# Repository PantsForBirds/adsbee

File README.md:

# ADSBee

ADSBee is a family of open-source, dual-band ADS-B receivers from [Pants for Birds LLC](https://pantsforbirds.com). Every ADSBee decodes 1090 MHz Mode S / ADS-B and 978 MHz UAT transmissions onboard — no SDR dongle, FPGA, or host computer required — maintains an aircraft dictionary, and streams tracked aircraft over UART (and, on the 1090 family, WiFi / Ethernet) in a wide range of output protocols. This repository holds the firmware, hardware design files, datasheets, and host software for the whole family.

There are two product lines, which share most of their firmware (`firmware/common/`):

| | **ADSBee 1090** | **ADSBee 1421** |
|---|---|---|
| Best for | Ground stations, feeders, networked receivers | Ultra-low-power embedded / UAS detect-and-avoid |
| Processors | RP2040 + ESP32-S3 + CC1312 | TI CC1314R10 + Semtech LR2021 |
| 1090 MHz | Custom RF frontend + RP2040 PIO decoder | LR2021 OOK receiver |
| 978 MHz UAT | CC1312 sub-GHz radio | CC1314 sub-GHz radio (uplink reception selectable) |
| Interfaces | USB, UART, WiFi, Ethernet (PoE pant / W5500), GNSS | UART (AT commands), SYNC line, LR2021 SPI passthrough |
| Power | ~1W | ~19 mA at 1.8–3.3 V |
| Firmware | [`firmware/adsbee_1090/`](firmware/adsbee_1090/) | [`firmware/adsbee_1421/`](firmware/adsbee_1421/) |

## Safety Notice

We work hard to make ADSBee products performant and reliable, but not all aircraft broadcast their location, messages can be lost or corrupted, and hardware or software can fail. ADSBee cannot guarantee detection or accurate reporting of all traffic. Users are responsible for evaluating its suitability for their application and for the safe operation of any system it is integrated into. See our [terms of sale](https://pantsforbirds.com/terms-of-sale/#warranty) and [license](LICENSE) for full terms.

## Products and Where to Buy

All ADSBee devices are designed and sold by Pants for Birds LLC. Purchasing a device is the best way to support the project. Product pages, datasheets, and the [Quick Start Guide](https://pantsforbirds.com/adsbee/quick-start/) live at [pantsforbirds.com](https://pantsforbirds.com/adsbee/).

### ADSBee 1090 family

| | |
|---|---|
|  | **[ADSBee 1090U](https://pantsforbirds.com/product/adsbee-1090u/)** — RP2040, ESP32-S3, CC1312, and a custom 1090 MHz RF frontend on a single PCBA, enabling all multi-band receive and networking functions (Ethernet requires an external pant). [Datasheet](word/exports/datasheet_adsbee_1090.pdf) |
|  | **[ADSBee m1090](https://pantsforbirds.com/product/adsbee-m1090/)** — solder-down module containing only the 1090 MHz frontend and RP2040. Add a CC1312 and ESP32 on your carrier board for the full 1090U feature set, running the same firmware image. Drops one of the 1090U's two LNA stages for lower power and better ultra-close-range performance; populate an external LNA on the carrier for equivalent maximum range. An [m1090 Eval Board](https://pantsforbirds.com/product/adsbee-m1090-eval-board/) is available ([datasheet](word/exports/datasheet_adsbee_m1090_eval_board.pdf)). |
|  | **[GS3M PoE](https://pantsforbirds.com/product/adsbee-gs3m-poe/)** — the ADSBee 1090U in a ruggedized, weatherproof enclosure, connected and powered over 802.3af Power over Ethernet for industrial and outdoor installations. [Datasheet](word/exports/datasheet_gs3m_poe.pdf) |

### ADSBee 1421 family

| | |
|---|---|
|  | **[ADSBee m1421](https://pantsforbirds.com/product/adsbee-m1421/)** — high-performance, ultra-low-power dual-band receiver module (TI CC1314R10 + Semtech LR2021). Receives 1090 MHz Mode S and 978 MHz UAT, tracks up to 400 aircraft onboard, and reports over UART. Weighs 1.85 g. [Datasheet](word/exports/datasheet_adsbee_m1421.pdf) |
|  | **[ADSBee 1421 Developer Kit](https://pantsforbirds.com/product/adsbee-1421-devkit/)** — compact carrier board for the m1421 with a power combiner so a single lightweight dual-band antenna feeds both the 1090 MHz and 978 MHz inputs. Includes the PCBA with ARM-JTAG header, wire harness, USB programmer, and a dual-band ADS-B antenna. [Datasheet](word/exports/datasheet_adsbee_1421_devkit.pdf) |

## ADSBee 1090

ADSBee 1090 is an open-source multi-band radio receiver and decoder for ADS-B packets transmitted by aircraft and ground stations. It is based on an RP2040 microcontroller and utilizes two independent PIO blocks to find and decode ADS-B messages without the need for an FPGA. ADSBee 1090 includes a radio receiver frontend with filtering and amplification, as well as a software-defined comparator circuit with an adjustable trigger threshold for customizable receive sensitivity in a diverse range of RF environments.

### Features
* Decoding of 1090 MHz transponder signals (ADS-B and Mode S).
* Decoding of 978 MHz UAT transponder signals (ADS-B) and uplink data (FIS-B/TIS-B).
* ADS-L (EASA ADS-L 4 SRD-860) receive on 868.2 or 868.4 MHz instead of UAT (`AT+SUBG_MODE=ADSL_RX`). ADS-L traffic shows in Aircraft JSON, the web UI, GDL90 and RAW (`#ADL*`). Senders alternate between the two channels, so one channel hears about half of their messages. The sub-GHz input is matched for 978 MHz; use an 868 MHz antenna. Firmware 0.11.0-rc1 and later.
* 1x USB console input / output for changing parameters and transmitting data.
* 1x UART for reporting data or ingesting GNSS information.
* Built-in EEPROM for storing nonvolatile settings.
* Feature-rich AT command set for customizing baud rates, output data protocols, signal conditioning values, etc.
* Multiple supported output protocols:
    * Raw packets
    * MAVLINK1
    * MAVLINK2
    * GDL90
    * Mode S Beast
    * Aircraft JSON
    * CSBee (custom information-rich ASCII protocol)
* 2.4 GHz 802.11 radio for automatic streaming of decoded values to custom endpoints on the internet. No external compute required, just add WiFi and power!
* Ethernet interface (requires external PoE pant or W5500 IC).
* GNSS module connector for MLAT and ground station location information.
* ~1W power draw.

### Architecture
ADSBee 1090 utilizes some basic RF hardware (SAW filters, LNA, logarithmic power detector) to amplify the received pulse-position-modulated ADS-B waveform into a pulse train that is conditioned by a comparator and fed to a PIO input pin on the RP2040. The RP2040 utilizes two PIO state machines, one for preamble detection and one for Manchester decoding of the message body, to decode the ADS-B message. This offers significant cost and power savings over FPGA-based solutions that solve the same problem.

A filtered PWM output from the RP2040 can be used to adjust the bias of the data slicer comparator circuit on the output of the receive signal chain, allowing logarithmic adjustments in receiver sensitivity which can be used to filter out weaker ADS-B signals in congested environments or maximize sensitivity for increased receive range.

There are two devices connected to the RP2040 via a common SPI bus: a CC1312 for secondary band receive and an ESP32-S3 for networking functions.

The CC1312 can be tuned to a variety of sub-GHz frequencies to decode UAT messages (and potentially more protocols in the future). These messages are forwarded to the RP2040 over SPI and reported through a unified interface along with the Mode S packets received by the RP2040.

The ESP32-S3 ingests raw packets from the RP2040 and maintains its own aircraft dictionary for reporting over network interfaces (WiFi, Ethernet). The RP2040's dictionary holds 400 aircraft for its USB and UART outputs; the ESP32-S3's holds 200.

All three microcontrollers utilize code stored on the RP2040's external flash chip, so firmware updates are conducted by flashing a single firmware image to the RP2040, which in turn flashes updated firmware images to the CC1312 and ESP32-S3.

## ADSBee 1421

ADSBee 1421 is an ultra-low-power dual band ADS-B receiver, built around a TI CC1314R10 low-power RF MCU and a Semtech LR2021 radio. The LR2021 provides best-in-class sensitivity for the high-baud-rate OOK 1090 MHz Mode S waveform, while the CC1314's sub-GHz RF core receives 978 MHz UAT and its Cortex-M33 does all demodulation, FEC, decoding, and aircraft tracking. The whole receiver draws about 19 mA and weighs under 2 g, making it suited to UAS detect-and-avoid and other power- and weight-constrained applications.

### Features
* Decoding of 1090 MHz transponder signals (ADS-B and Mode S), with selectable preamble modes for range vs. message-type coverage (`AT+R1090_PREAMBLE`).
* Decoding of 978 MHz UAT transponder signals (ADS-B) and ground uplink data (FIS-B/TIS-B). Uplink reception can be disabled independently (`AT+SUBG_MODE=UAT_RX_NO_UPLINK`) to save airtime and CPU when only traffic is needed.
* ADS-L (EASA ADS-L 4 SRD-860) receive on 868.2 or 868.4 MHz instead of UAT (`AT+SUBG_MODE=ADSL_RX`), reported in Aircraft JSON, GDL90 and RAW (`#ADL*`). The m1421 sub-GHz filter passes 770-928 MHz. Firmware 0.5.0-rc1 and later.
* Onboard aircraft dictionary for up to 400 simultaneous targets.
* UART console with a feature-rich AT command set (baud rate, output protocol, receiver position, gain, logging, …); settings persist in flash.
* Multiple supported output protocols: Raw packets, CSBee, MAVLINK1, MAVLINK2, GDL90, Mode S Beast, Aircraft JSON.
* SYNC line for host-controlled deep sleep (STANDBY with SRAM retained), which also hands the LR2021 SPI bus to an external MCU — e.g. to use the LR2021's 2.4 GHz radio for LoRa or mesh networking.
* Firmware updates over the UART ROM bootloader (no debugger needed) or JTAG. Holding SYNC high through a reset enters the bootloader, so any host that drives a USB-UART adapter's RTS → SYNC and DTR → RESET_N (or the included ADSBee 1421 Programmer) can reflash the module remotely. See [Reflashing over UART: the SYNC bootloader backdoor](firmware/adsbee_1421/README.md#reflashing-over-uart-the-sync-bootloader-backdoor).
* Ultra-low power: ~19 mA at 1.8–3.3 V.

### Architecture
The CC1314R10 runs a NoRTOS super-loop: it polls the LR2021 over SPI for 1090 MHz OOK frames, services its own RF core's UAT receptions (ADS-B and uplink are distinguished by sync word, so uplink can be switched off at the radio), runs the shared Mode S / UAT decoders and aircraft dictionary from `firmware/common/`, and reports over the console UART. A host can suspend the device by driving SYNC high; on wake the receiver re-initializes itself. SYNC is also the ROM bootloader backdoor pin, so a reset while SYNC is high enters the serial bootloader. See [`firmware/adsbee_1421/AGENTS.md`](firmware/adsbee_1421/AGENTS.md) for the build guide and the SYNC sleep / LR2021 bus-handoff contract, and the [m1421 datasheet](word/exports/datasheet_adsbee_m1421.pdf) for the full AT command reference.

## Repository Layout

| Path | Contents |
|---|---|
| [`firmware/`](firmware/) | All firmware. [`adsbee_1090/`](firmware/adsbee_1090/) (RP2040 `pico/`, `esp/`, CC1312 `ti/`), [`adsbee_1421/`](firmware/adsbee_1421/) (CC1314 `ti/`, RP2040-Zero `programmer/`, the ADSBee 1421 Programmer), [`common/`](firmware/common/) (shared decoders, aircraft dictionary, comms, settings), `modules/` (submodules: cppAT, googletest, …), [`scripts/`](firmware/scripts/) (dev tooling), [`build.sh`](firmware/build.sh) dispatcher. |
| [`software/`](software/) | Host software: [`adsbee_1421_console/`](software/adsbee_1421_console/) (single-file Web Serial console + UART flasher for the 1421), `adsbee/` (Python package), `serial_logger/`, and `tar1090/` / `ultrafeeder/` / `ultra2/` feeder compose files. |
| [`ci/`](ci/) | Hardware-in-the-loop USB/UF2 + OTA flash test run by the self-hosted CI runner. |
| [`kicad/`](kicad/) | Hardware design files (ADSBee 1090, 1090U, frontend prototypes, panels). |
| [`3d/`](3d/) | Enclosure exports and CAD links. |
| [`ltspice/`](ltspice/), [`excel/`](excel/) | RF / analog simulations and design calculations. |
| [`affinity/`](affinity/) | Diagrams and promotional artwork sources. |
| [`word/`](word/) | Product datasheets and firmware reference guide (`.docx` sources, PDFs in [`word/exports/`](word/exports/)). |
| [`references/`](references/) | Protocol specifications and component datasheets. |
| [`images/`](images/) | Images used by this README. |

## Building and Flashing Firmware

All toolchains live in Docker containers, so the only host requirements are Docker and git.

```bash
git clone https://github.com/CoolNamesAllTaken/adsbee.git
cd adsbee
bash firmware/scripts/setup_dev.sh        # init submodules + install the pre-commit version-check hook
bash firmware/build.sh adsbee_1090        # RP2040 + ESP32-S3 + CC1312 -> combined.uf2
bash firmware/build.sh adsbee_1421        # CC1314R10 -> adsbee_1421-<version>.hex
```

* **[`firmware/README.md`](firmware/README.md)** — prerequisites, the build dispatcher, build targets and outputs.
* **[`firmware/AGENTS.md`](firmware/AGENTS.md)** — firmware architecture overview and the version-management rules.
* **ADSBee 1090:** [`firmware/adsbee_1090/Developers_Guide.md`](firmware/adsbee_1090/Developers_Guide.md) covers the three-processor build order, flashing (`combined.uf2` over USB BOOTSEL, or OTA through the ESP32 web interface), and recovery.
* **ADSBee 1421:** [`firmware/adsbee_1421/AGENTS.md`](firmware/adsbee_1421/AGENTS.md) covers the build; flash over JTAG with a J-Link ([`firmware/adsbee_1421/ti/README.md`](firmware/adsbee_1421/ti/README.md)), or over UART using the ROM bootloader ([SYNC bootloader backdoor](firmware/adsbee_1421/README.md#reflashing-over-uart-the-sync-bootloader-backdoor)) via the [ADSBee 1421 Programmer](firmware/adsbee_1421/programmer/README.md) (an RP2040-Zero board included in the Developer Kit), a host script driving RTS/DTR, or the **Upload Firmware** button in the [web console](software/adsbee_1421_console/README.md).

Prebuilt firmware is published on the [Releases page](https://github.com/CoolNamesAllTaken/adsbee/releases). Releases are tagged per product as `adsbee_1090-<major>.<minor>.<patch>` and `adsbee_1421-<major>.<minor>.<patch>` (release candidates carry an `-rcN` suffix). `AT+DEVICE_INFO?` reports the firmware version running on a device.

## Support, Bugs, and Feature Requests

* **Getting started / using a device:** start with the [Quick Start Guide](https://pantsforbirds.com/adsbee/quick-start/) and the product datasheets in [`word/exports/`](word/exports/) (AT command reference, reporting protocols, pinouts).
* **Purchasing, orders, warranty, and hardware support:** contact Pants for Birds through [pantsforbirds.com/contact](https://pantsforbirds.com/contact/).
* **Firmware / software bugs:** open a [GitHub Issue](https://github.com/CoolNamesAllTaken/adsbee/issues). Please include:
  * which product (1090U, m1090, GS3M PoE, m1421, 1421 Developer Kit) and the output of `AT+DEVICE_INFO?` (part code and firmware version);
  * what you expected vs. what happened, and steps to reproduce;
  * relevant console output (`AT+LOG_LEVEL=INFO` makes the device chattier) and, for the 1090 family, the web interface/feed configuration involved.
* **Feature requests and questions:** also welcome as GitHub Issues; please tag the title with the product family.

## Contributing

Contributions are welcome (bug fixes, new output protocols, decoder improvements, documentation, etc)! Please follow the steps below to contribute a change.

1. Fork the repo and create a branch from `main`.
2. Run `bash firmware/scripts/setup_dev.sh` once. It initializes submodules and installs a git pre-commit hook that enforces the version rule below.
3. Make your change. Any change under `firmware/adsbee_1090/`, `firmware/adsbee_1421/`, or `firmware/common/` must ship under a firmware version that has not been released yet for the affected product(s) (`firmware/common/coprocessor/object_dictionary.cpp` for 1090, `firmware/adsbee_1421/ti/object_dictionary/object_dictionary.cpp` for 1421; a `common/` change concerns both). If main is already on the next unreleased RC, keep it; if its version matches a release tag, move to the next unreleased RC. Note that devices only reflash coprocessors on a version mismatch, so you will need to force a reflash or bump the software version to test your code [`firmware/AGENTS.md`](firmware/AGENTS.md). When have finished testing and go to you submit your PR, ensure that your firmware version matches the version string in main! Firmware versions are only rolled upon each release.
4. If you add or change an AT command, reporting protocol, or other user-visible behavior, update the corresponding datasheet in [`word/`](word/).
5. Build locally with `firmware/build.sh` and, for 1090 changes, run the host unit tests (`bash firmware/build.sh adsbee_1090 test`).
6. Open a pull request against `main`. [CI](https://github.com/CoolNamesAllTaken/adsbee/actions/workflows/firmware.yml) builds every target and runs the unit tests; the hardware-in-the-loop flash test runs on `main` after merge.

By contributing you agree that your contributions are licensed under the GPL-3.0.

## License

ADSBee firmware, software, and design files in this repository are released under the [GNU General Public License v3.0](LICENSE). ADSBee is a product of Pants for Birds LLC.

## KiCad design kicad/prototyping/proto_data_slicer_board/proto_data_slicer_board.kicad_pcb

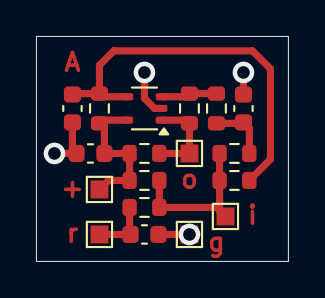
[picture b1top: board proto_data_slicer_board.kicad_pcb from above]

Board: 2 copper layers, 14.0 x 12.5 mm, 18 parts (0 on the bottom side), 8 nets.

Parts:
C1: 100pF; C_0603_1608Metric
C2: 0.1uF; C_0603_1608Metric
C3: 3pF; C_0603_1608Metric
C4: 10nF; C_0603_1608Metric
R1, R3, R4: 10k; R_0603_1608Metric
R2, R5: 1M; R_0603_1608Metric
R6, R7, R8: 1k; R_0603_1608Metric
TP1, TP2, TP3, TP4, TP5: TestPoint; TestPoint_Pad_1.0x1.0mm
U1: MCP6566; SOT-353_SC-70-5

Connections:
+3V3: C2.1, R2.1, R7.1, R8.1, TP5.1, U1.5 (V+)
/IN: R1.1, R3.1, R6.1, R7.2, TP1.1
/LEVEL: C1.1, R1.2, R2.2, U1.4 (-)
/OUT: R5.2, R8.2, TP2.1, U1.1
/PULSE: C3.1, R3.2, R4.1
/PULSE': R4.2, R5.1, U1.3 (+)
/RSSI: C4.1, R6.2, TP3.1
GND: C1.2, C2.2, C3.2, C4.2, TP4.1, U1.2 (V-)

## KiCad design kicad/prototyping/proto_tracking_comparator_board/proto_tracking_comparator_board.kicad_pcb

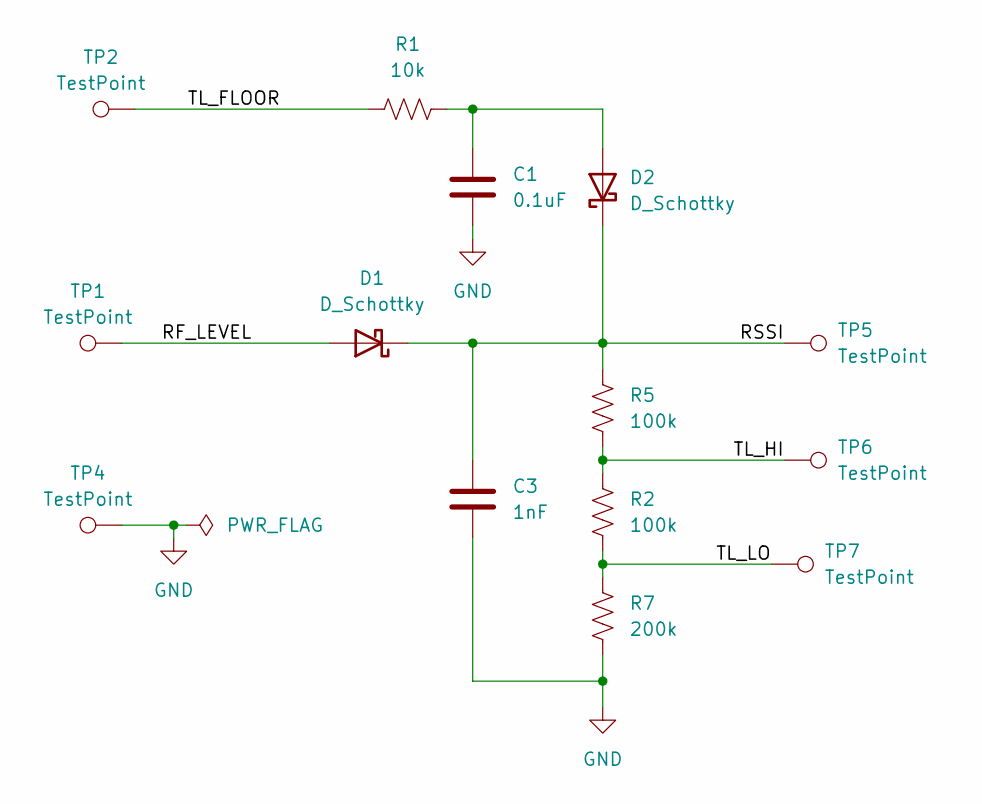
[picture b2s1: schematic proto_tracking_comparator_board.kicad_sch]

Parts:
C1: 0.1uF; C_0603_1608Metric
C3: 1nF; C_0603_1608Metric
D1, D2: D_Schottky; D_0402_1005Metric
R1: 10k; R_0603_1608Metric
R2, R5: 100k; R_0603_1608Metric
R7: 200k; R_0603_1608Metric
TP1, TP2, TP4, TP5, TP6, TP7: TestPoint; TestPoint_Pad_1.0x1.0mm

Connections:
/RF_LEVEL: D1.2 (A), TP1.1
/RSSI: C3.1, D1.1 (K), D2.1 (K), R5.2, TP5.1
/TL_FLOOR: R1.2, TP2.1
/TL_HI: R2.2, R5.1, TP6.1
/TL_LO: R2.1, R7.2, TP7.1
GND: C1.2, C3.2, R7.1, TP4.1
unnamed: C1.1, D2.2 (A), R1.1

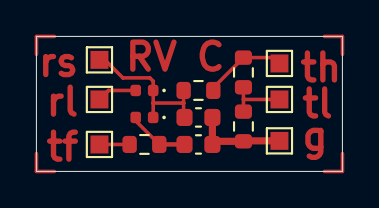
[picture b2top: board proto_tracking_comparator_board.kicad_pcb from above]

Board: 2 copper layers, 17.0 x 7.5 mm, 14 parts (0 on the bottom side), 7 nets.

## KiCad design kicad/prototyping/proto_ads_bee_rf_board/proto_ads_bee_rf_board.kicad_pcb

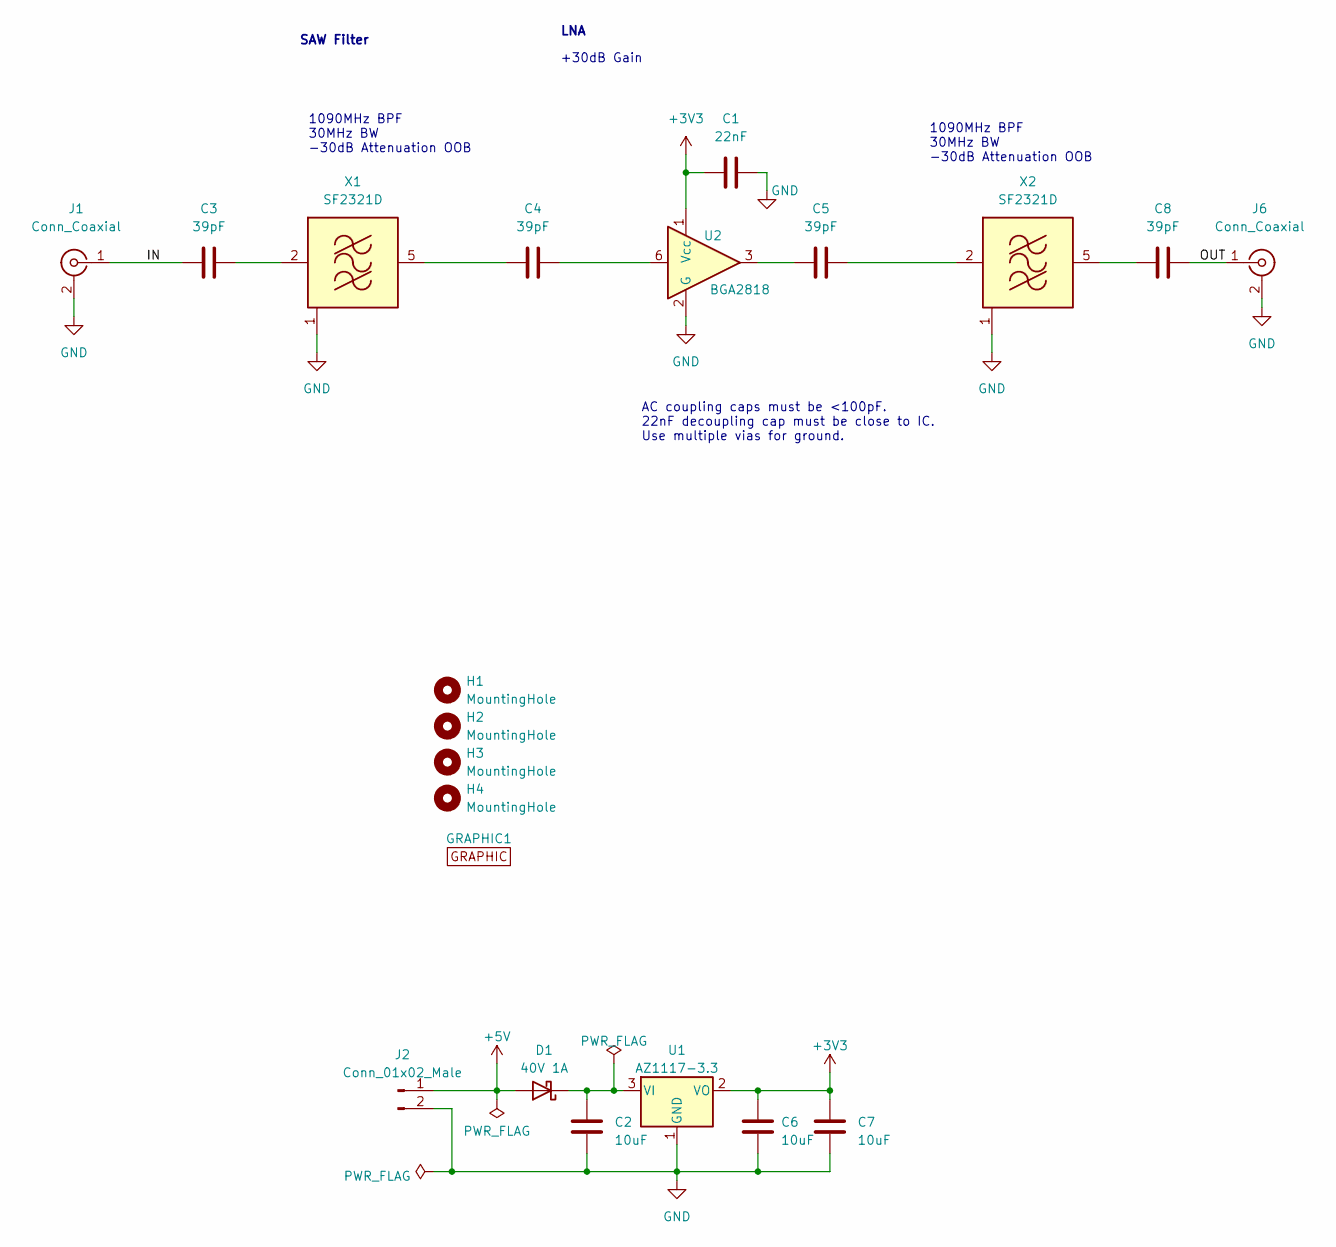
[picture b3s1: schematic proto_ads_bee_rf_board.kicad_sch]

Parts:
C1: 22nF; C_0603_1608Metric
C2, C6, C7: 10uF; C_0805_2012Metric
C3, C4, C5, C8: 39pF; C_0603_1608Metric
D1: 40V 1A; D_DO-41_SOD81_P7.62mm_Horizontal; MPN 1N5819
GRAPHIC1: Graphic; bird_with_pants_small_flipped
H1, H2, H3, H4: MountingHole; MountingHole_3.2mm_M3
J1, J6: Conn_Coaxial; SMA_Amphenol_132289_EdgeMount; MPN 132289
J2: Conn_01x02_Male; PinHeader_1x02_P2.54mm_Horizontal
U1: AZ1117-3.3; SOT-223-3_TabPin2
U2: BGA2818; SOT-363_SC-70-6
X1, X2: SF2321D; Filter_SAW-6_3.8x3.8mm; MPN SF2321D

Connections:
+3V3: C1.1, C6.1, C7.1, U1.2 (VO), U2.1 (Vcc)
+5V: D1.2 (A), J2.1
/IN: C3.1, J1.1 (In)
/OUT: C8.2, J6.1 (In)
GND: C1.2, C2.2, C6.2, C7.2, J1.2 (Ext), J2.2, J6.2 (Ext), U1.1 (GND), U2.2 (G), U2.4 (G), U2.5 (G), X1.1 (GND), X1.3 (GND), X1.4 (GND), X1.6 (GND), X2.1 (GND), X2.3 (GND), X2.4 (GND), X2.6 (GND)
unnamed: C4.2, U2.6
unnamed: C5.1, U2.3
unnamed: C2.1, D1.1 (K), U1.3 (VI)
unnamed: C3.2, X1.2 (IN)
unnamed: C4.1, X1.5 (OUT)
unnamed: C5.2, X2.2 (IN)
unnamed: C8.1, X2.5 (OUT)

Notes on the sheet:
LNA
+30dB Gain
1090MHz BPF 30MHz BW -30dB Attenuation OOB
SAW Filter
AC coupling caps must be <100pF. 22nF decoupling cap must be close to IC. Use multiple vias for ground.

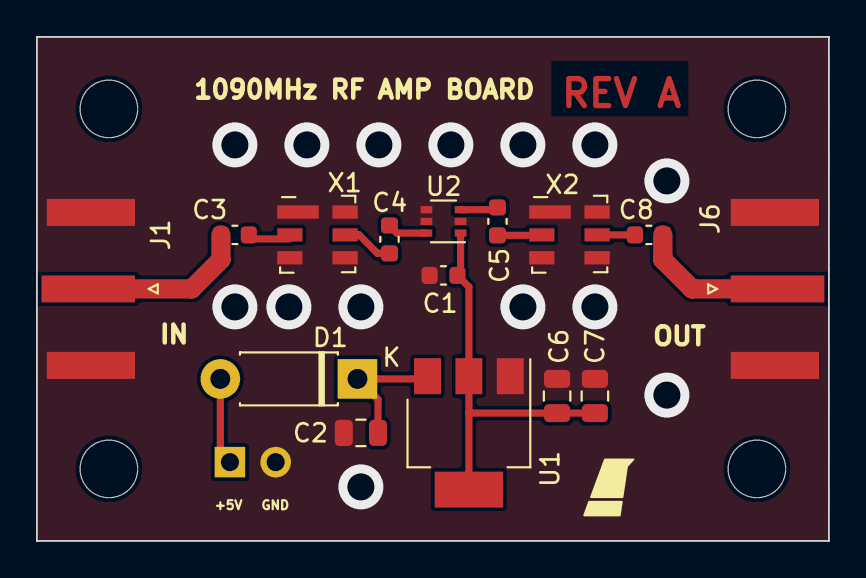
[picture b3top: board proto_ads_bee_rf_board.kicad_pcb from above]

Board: 2 copper layers, 44.0 x 28.0 mm, 21 parts (1 on the bottom side), 12 nets.

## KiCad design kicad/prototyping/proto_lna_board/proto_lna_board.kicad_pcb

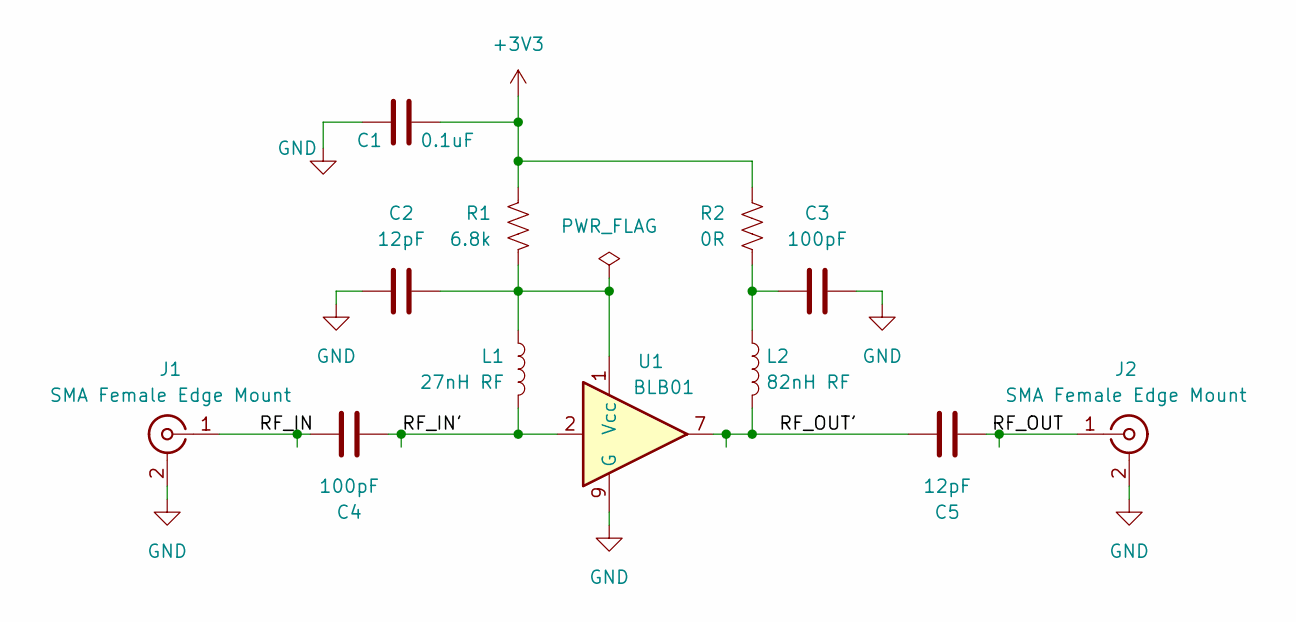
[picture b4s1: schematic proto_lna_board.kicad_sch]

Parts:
C1: 0.1uF; C_0402_1005Metric; MPN C60474
C2, C5: 12pF; C_0402_1005Metric; MPN C326662
C3, C4: 100pF; C_0402_1005Metric; MPN C106200
J1, J2: SMA Female Edge Mount; SMA_Amphenol_132289_EdgeMount
L1: 27nH RF; L_0402_1005Metric; MPN C408697
L2: 82nH RF; L_0402_1005Metric; MPN C54972
R1: 6.8k; R_0402_1005Metric; MPN C93940
R2: 0R; R_0402_1005Metric; MPN C60485
U1: BLB01; DFN-8-1EP_2x2mm_P0.5mm_EP0.9x1.5mm

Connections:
+3V3: C1.1, R1.1, R2.1
/RF_IN: C4.1, J1.1 (In)
/RF_IN': C4.2, L1.2, U1.2
/RF_OUT: C5.2, J2.1 (In)
/RF_OUT': C5.1, L2.2, U1.7
GND: C1.2, C2.1, C3.2, J1.2 (Ext), J2.2 (Ext), U1.9 (G)
unnamed: C3.1, L2.1, R2.2
unnamed: C2.2, L1.1, R1.2, U1.1 (Vcc)

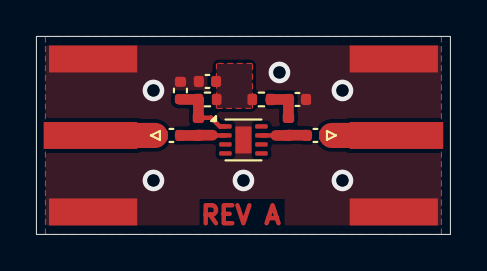
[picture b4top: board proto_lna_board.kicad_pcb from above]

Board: 2 copper layers, 23.0 x 11.0 mm, 12 parts (0 on the bottom side), 8 nets.

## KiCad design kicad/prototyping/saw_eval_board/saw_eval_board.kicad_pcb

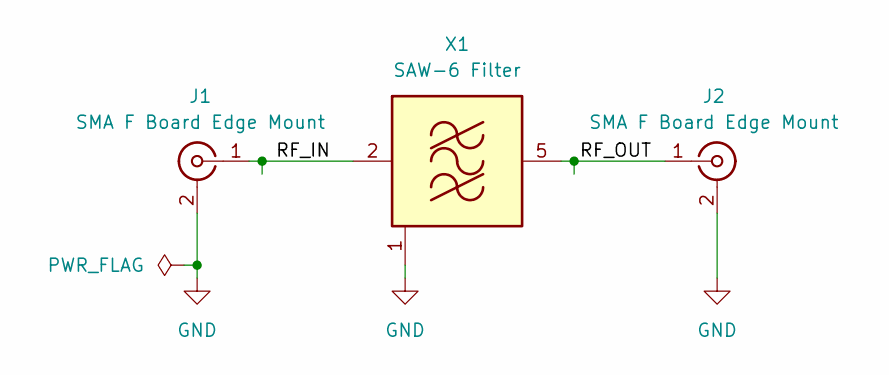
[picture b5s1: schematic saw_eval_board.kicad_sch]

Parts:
J1, J2: SMA F Board Edge Mount; SMA_Amphenol_132289_EdgeMount
X1: SAW-6 Filter; Filter_SAW-6_3.0x3.0mm

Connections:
/RF_IN: J1.1 (In), X1.2 (IN)
/RF_OUT: J2.1 (In), X1.5 (OUT)
GND: J1.2 (Ext), J2.2 (Ext), X1.1 (GND), X1.3 (GND), X1.4 (GND), X1.6 (GND)

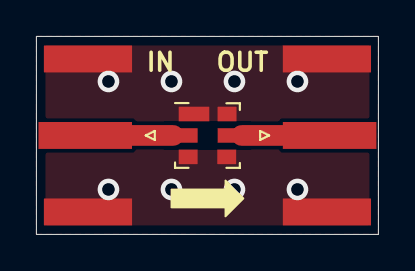
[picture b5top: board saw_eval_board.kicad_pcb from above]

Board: 2 copper layers, 19.0 x 11.0 mm, 3 parts (0 on the bottom side), 3 nets.

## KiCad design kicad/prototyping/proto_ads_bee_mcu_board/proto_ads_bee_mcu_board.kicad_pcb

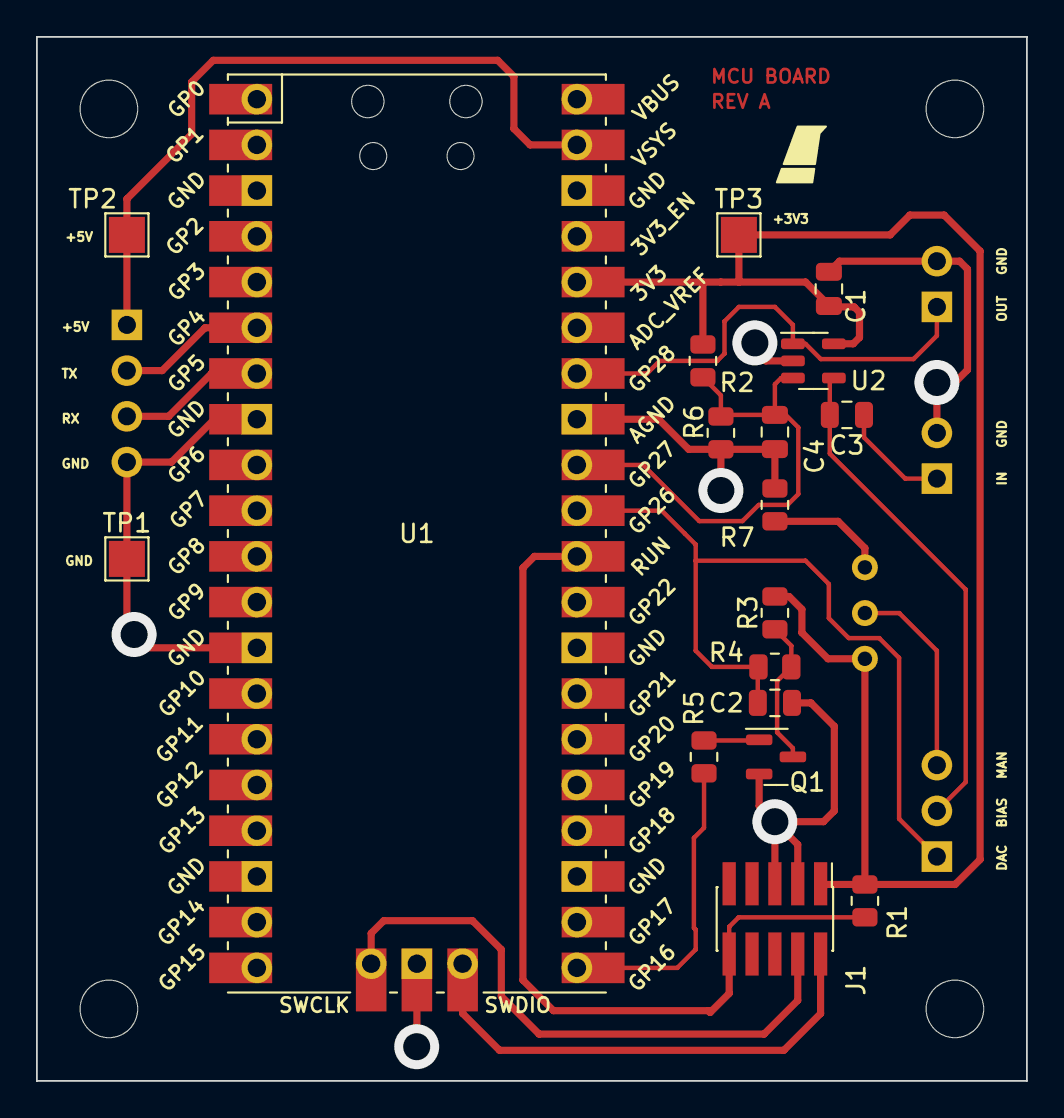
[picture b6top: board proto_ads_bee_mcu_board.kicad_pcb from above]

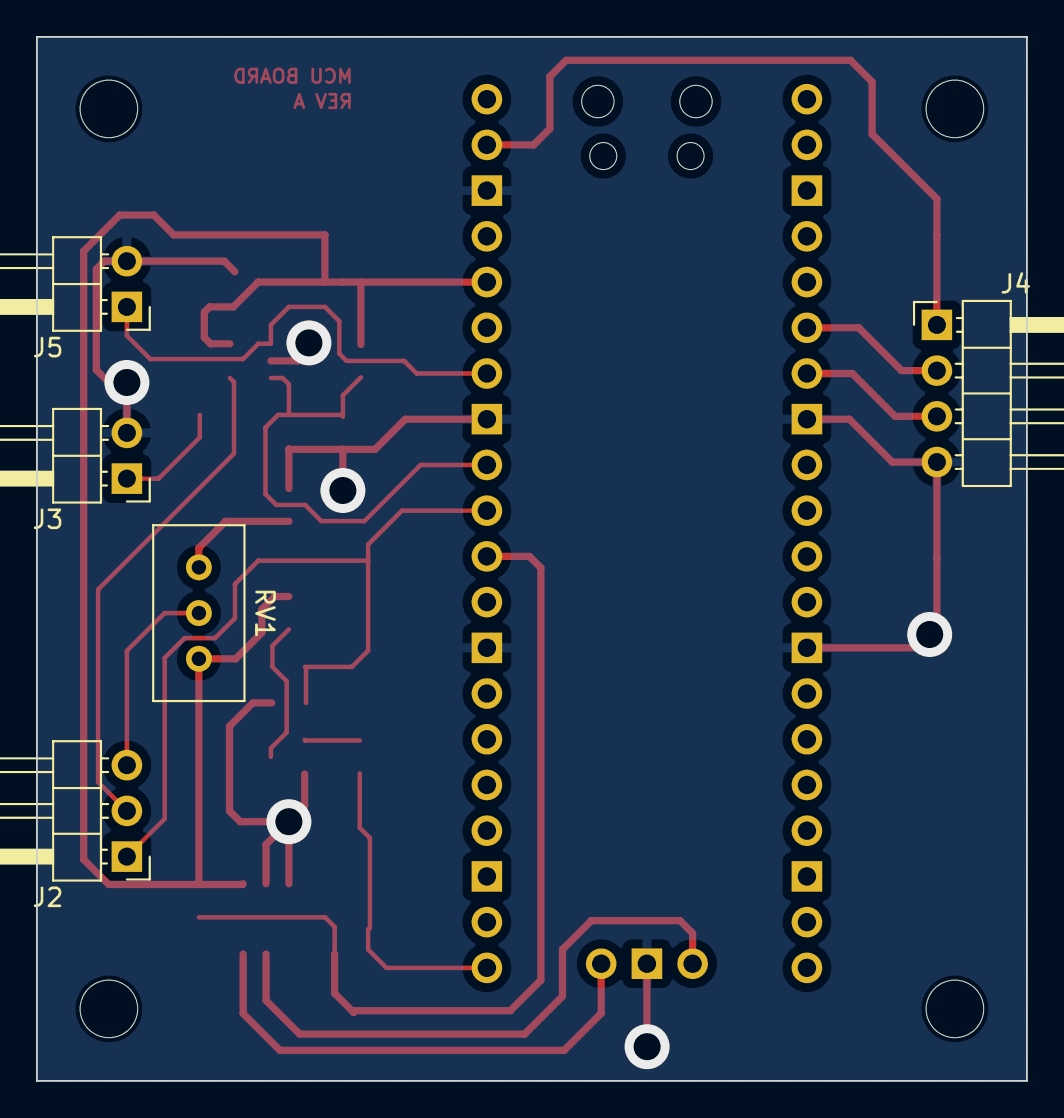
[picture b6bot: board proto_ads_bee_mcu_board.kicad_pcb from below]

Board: 2 copper layers, 55.0 x 58.0 mm, 29 parts (5 on the bottom side), 18 nets.

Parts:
C1, C2, C4: 0.1uF; C_0805_2012Metric
C3: 1uF; C_0805_2012Metric
GRAPHIC1: Graphic; bird_with_pants_small_flipped
H1, H2, H3, H4: MountingHole; MountingHole_3.2mm_M3
J1: Conn_ARM_JTAG_SWD_10; PinHeader_2x05_P1.27mm_Vertical_SMD
J2: Conn_01x03_Pin; PinHeader_1x03_P2.54mm_Horizontal
J3, J5: Conn_01x02_Pin; PinHeader_1x02_P2.54mm_Horizontal
J4: Conn_01x04_Pin; PinHeader_1x04_P2.54mm_Horizontal
PCB1: PCB; PCB_PN_REV_small
Q1: 2N7002; SOT-23
R1, R2, R4: 10k; R_0805_2012Metric
R3: 1k; R_0805_2012Metric
R5: 100; R_0805_2012Metric
R6, R7: 4.99k; R_0805_2012Metric
RV1: 10k; Potentiometer_Bourns_3296W_Vertical
TP1, TP2, TP3: TestPoint; TestPoint_Pad_2.0x2.0mm
U1: Pico; RPi_Pico_SMD_TH
U2: MCP6541; SOT-23-5

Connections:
+3V3: C1.1, J1.1 (VTref), R1.1, R2.1, R3.1, RV1.1, TP3.1, U1.36 (3V3), U2.5 (V+)
+5V: J4.1, TP2.1, U1.39 (VSYS)
/COMP_BIAS_DC: C2.1, J2.1, R4.2, U1.31 (GPIO26_ADC0)
/COMP_BIAS_PWM: R5.1, U1.21 (GPIO16)
/COMP_OUT: J5.1, U1.34 (GPIO28_ADC2), U2.1
/COMP_REF: C4.1, R2.2, R6.1, U1.32 (GPIO27_ADC1), U2.3 (+)
/COMP_SIG: C3.2, J2.2, U2.4 (-)
/UART_RX: J4.3, U1.7 (GPIO5)
/UART_TX: J4.2, U1.6 (GPIO4)
/V_DN: C3.1, J3.1
/~RESET: J1.10 (~RESET), R1.2, U1.30 (RUN)
GND: C1.2, C2.2, C4.2, J1.3 (GND), J1.5 (GND), J3.2, J4.4, J5.2, Q1.2 (S), R6.2, R7.2, TP1.1, U1.8 (GND), U1.13 (GND), U1.28 (GND), U1.33 (AGND), U1.38 (GND), U1.42 (GND), U2.2 (V-)
unnamed: J1.4 (SWDCLK/TCK), U1.41 (SWCLK)
unnamed: J1.2 (SWDIO/TMS), U1.43 (SWDIO)
unnamed: J2.3, RV1.2
unnamed: Q1.3 (D), R3.2, R4.1
unnamed: Q1.1 (G), R5.2
unnamed: R7.1, RV1.3

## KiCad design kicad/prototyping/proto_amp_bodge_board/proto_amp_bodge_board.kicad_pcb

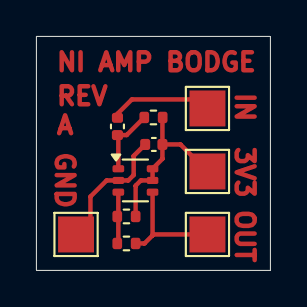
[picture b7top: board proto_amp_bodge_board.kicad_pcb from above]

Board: 2 copper layers, 13.0 x 13.0 mm, 10 parts (0 on the bottom side), 6 nets.

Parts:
C1: 0.1uF; C_0402_1005Metric
C2: 22nF; C_0402_1005Metric
R1, R2: 10k; R_0402_1005Metric
R3: 100k; R_0402_1005Metric
TP1, TP2, TP3, TP4: TestPoint; TestPoint_Pad_2.0x2.0mm
U1: OPA358AIDCKR; SOT-363_SC-70-6

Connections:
+3V3: C1.1, R1.1, R2.1, TP3.1, U1.5 (ENABLE), U1.6 (V+)
GND: C1.2, TP4.1, U1.2 (V-)
unnamed: C2.1, TP2.1
unnamed: R3.2, TP1.1, U1.4
unnamed: C2.2, R1.2, U1.1 (+)
unnamed: R2.2, R3.1, U1.3 (-)

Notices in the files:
README.md:
License: GPL-3.0
